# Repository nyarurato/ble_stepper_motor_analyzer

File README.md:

# BLE Stepper Motor Monitor

The BLE Stepper Monitor Analyzer is a variant of the Simple Stepper Motor Analyzer which replaces the touch screen LCD with a Bluetooth BLE radio link and a python app that provides the display or a desktop computer. This result in a smaller and less expensive board and a large display that leverages on the desktop computer capabilities.

## Highlights
* Open-source hardware, firmware, and software designs, with permissive license that allows commercial use and does not require attribution.
* A small and relatively inexpensive PCB that can be embedded in a 3D printer or CNC machine.
* Each PCB has a unique address and can be monitored individually.
* The PCB's can be ordered  from JLCPCB with all the parts preassembled, except for the the nrf52 BLE module that need to be soldered separately.
* The stepper motor is galvanically isolated from the analyzer's electronics which  minimizes potential interference or ground loops.
* The analyzer can be powered from any 4.5 to 30VDC source and consumes very little power, about 50mw. Even a single 9V battery can power it for many hours. Power is required only when monitoring the stepper and the stepper can be operates safely even if the PCB is not powered.

## Caveats
* At this time, updating the PCB firmware requires a programmer. Normally it can be an inexpensive Segger JLink EDU Mini, which as of Aug 2022 are unavailable due to the global supply chain shortage. A more expensive alternative is the Nordic nRF52832 DK which can act also as a Segger programmer.
* The two current sensor ICs that are available from JLCPCB have higher noise than the Alegro GMR sensors. However, the analyzer functions properly with the noisier sensors as well.
* As of Aug 2022, the python application requires some TLC, for example to recover gracefully if a wireless connection lost. However, it is fully functional and was tested on Windows and Mac OSX.
* The PCB can be built with two versions of the BLE module, one with an internal antenna and one with a U.FL connector for an external antenna. Internal antennas are 
more compact but may be insufficient with shielded 3D printers.

## Installing the PCB

* IMPORTANT: Always turn power off before connecting or disconnecting the PCB or the stepper motor.
* Connect a voltage of 4.5VDC t0 30VDC to the connector J3. Pay attention to polarity though the PCB is protected against reversed polarity. Verify that one red LED is solid while the other blinks slowly.;
* With the PCB energized and the **stepper not connected yet to the board** long press on the PCB button until the yellow LED will blink. Make sure the LED blinked exactly 3 times. This will calibrate the zero current of the sensors.
* With power off, connect the 4 wires of your stepper motor through the board such that one connector with four wires is connected to your controller and the other is connected to the stepper. The PCB is arranged such that the 4 connector pins from left to right are connected pass-through to their respective pins on the other connector. Also, the two connector are interchangeable such that each can act as an input or an output.
* Turn power on and verify that your machine functions properly and that the direction of the stepper is correct. That is, the wiring should not reverse the direction of the stepper.

## Installing and running the Python application.

1. Download the python directory this github repository.
1. Install python3 on your computer. Follow the Python installation instructions for your operating system. The analyzer requires Python 3.7 or latter but prefer the latest available python. 
1. Identify the *python* and *pip* command on your computer. On some computers they can be *python* and *pip* respectively and on others something like *python3.10& and *pip3.10* respectively. From now on we will refer to them as *python* and *pip* but replace with the actual command names as needed.
1. Verify the version of your python by running the command: **python --version**. Verify that the printed version number is at least 3.7.
1. With the PCB powered, Run the command  *python3 scanner_main.py*, after a few seconds, it will print a list of BLE devices it found. One of them should have the name that looks like STP-XXXXXXXXXXXX. Note the device
address that is printed before that name. We will use it later to access
the device.
1. Run the command **python analyzer_main.py -d <device-address>** where <device-address> is the device address you identified in the previous step. If you get errors about missing python modules such as **bleak**, install them using the pip command and try again. You can also use the
**requirements.txt** file to install all missing modules at once.
1. If everything went well, the analyzer_main.py application will connect to the device and shows its data in real time.

## Understanding the data
The screenshot below shows the 8 data items that are monitors. The data can be reset using the **Reset** button and can be paused/played using the **Pause/Continue** button. 

1. Step counter over time. If the direction of the counting is opposite to what you would like, click on the **Toggle Dir** button. This will not effect the stepper motor but will count in the opposite direction.
2. Speed in steps/sec over time. This value is the derivative of the step counter above.
3. Stepper current in Amps over time. This value is computed as *sqrt(A^2 + B^2)* where A and B are the momentary currents in Amps in coils A, B respectively, and it represents the peak currents in each of the coils.
4. Coil peak current vs speed. This histogram shows the stepper current in different speeds. Ideally all speeds should have about the same current but too high inductance or too lower supply voltage may result in current and torque degradation in higher speeds.
5. Distance vs speed. This histogram shows in what speeds the stepper made the most distance (steps or revolutions)
6. Time vs speed. This histogram shows in what speeds the stepper was most of the time.
7. Phase pattern. This graph shows the 'cleanness' of the signal in the stepper coil. Every second of two the analyzer captures the signals in graph 8 and shows their pattern also in graph 7. Ideally graph 7 would be a circle center around the 0,0 point and its radius is the peak current set for the stepper.
8. Oscilloscope graph. This graph shows current patterns captures periodically from the two coils and ideally they should look like clean sin/cosine graphs with magnitude equal to the stepper peak current. Every cycle of the sin/cosine graph represent 4 full stepper steps. If the stepper speed is too fast or two slow to show the signals, use the Time Scale button to speed up or slow down the signal capture.

## Building your own BLE Stepper Motor Analyzer

* The three production files for JLCPCB SMD service are available under the kicad directory. This will allow you to get fully populated boards except for the BLE module.
* Solder a Raytac nrf52832 BLE module. You can use MDBT42Q-512KV2 (internal antenna) or MDBT42Q-U512KV2 (U.FL connector for an external antenna).
* Flash the board with the firmware using a compatible SWD programmer. We are using Segger's JLink with a Segger Edu Mini programmer or if this is not available, a Nordic NRF52-DK which can act also as a JLink programmer. Use a standard 2x5 pins 0.05" pitch SWD cable.
* Zero calibrate the sensors as explained above. 

## Modifying the firmware

* The source code of the firmware is available in this github repository under the platformio folder. Open that folder with the platformio IDE (a plugin for VSCode) and your project is ready.
* The PCB has a serial output for debugging. You can connect there a 115200 baud 3.3v serial/USB and view the output.
* To program the PCB use a Segger compatible debugger such as Segger Edu Mini, or Nordic nrf52 DK board. This will also allow you to debug the program, set breakpoints, single step and so on.

## FAQ

Q: Can I use this open source design in commercial products?

A: Yes, and you are welcome to do so, and attribution is not needed.

-----

Q: Can I operate the printer with the PCB connected but not powered or not monitored?

A: Yes. The electronics and the stepper are isolated from each other.

----

Q: How much does it cost to build the PCB?

A: Depending on quantities. For a batch of 30, JLCPCB changes about $7 per assembled board and then you need to add the Raytac BLE module which costs about $9. This brings the unit cost to less than $20, as of Aug 2022.

----

Q: If you would redesign it from scratch, what would you do differntly?

A: The main change would be to use ESP32 instead of the Raytac/Nordic module and this is for several reasons:

* It's less expensive.
* It has better support for firmware upgrade by the user.
* It's available from JLCPCB's SMD assembly service.

The Nordic nrf52 was selected for it's low power, with the intention to power the PCB by harvesting stepper motor power, but that requirement was dropped at a latter stages of the project.

-----

Q: How does this differs from the Simple Stepper Motor analyzer?

A: Some of the differences are:

* The lack of builtin display makes this analyzer more compact and less expensive.
* The Simple Stepper Motor analyzer is self contained with display while this one is intended to be buried in a 3D printer, using a computer for the display.
* The Simple Stepper Motor Analyzer uses a Raspberry Pi Pico processor while this one uses Nordic nRF52832.
* The Simple Stepper Motor Analyzer samples the signal at 100Khz while this one samples at 40Khz due to the limitations of the nRF52832. This however doesn't seem to matter.
* The Simple Stepper Motor Analyzer displays each graph on screen of its own while this one displays all the graphs at once.
* Having the display on a computer makes it easier to graph screenshots, for example, to post in diagnostics discussions in 3D printer forums.

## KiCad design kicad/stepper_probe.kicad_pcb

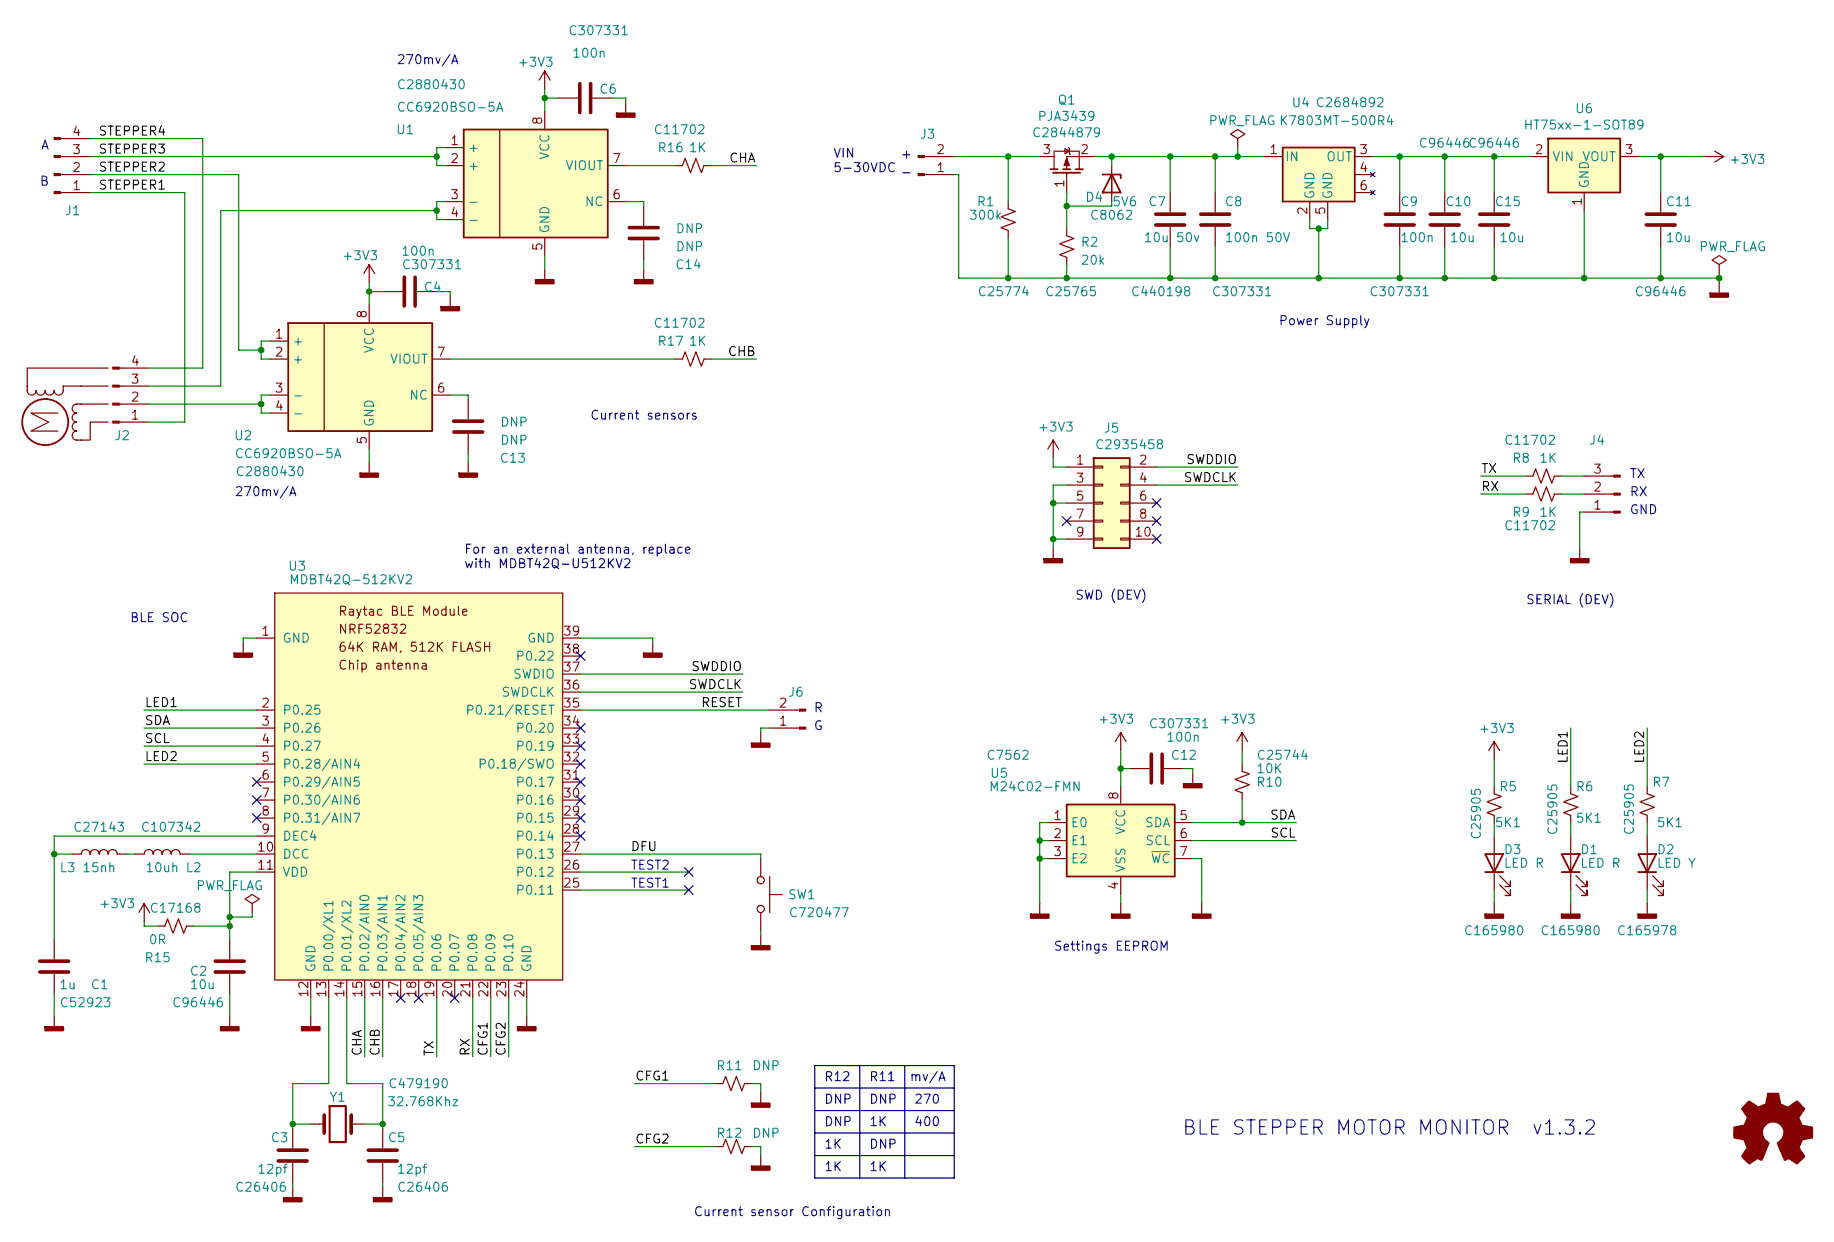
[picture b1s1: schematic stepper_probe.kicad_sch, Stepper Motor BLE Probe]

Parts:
C1: 1u; C_0402_1005Metric_Pad0.74x0.62mm_HandSolder; LCSC C52923
C2, C10, C11, C15: 10u; C_0603_1608Metric_Pad1.08x0.95mm_HandSolder; LCSC C96446
C3, C5: 12pf; C_0402_1005Metric_Pad0.74x0.62mm_HandSolder; LCSC C26406
C4, C6, C9, C12: 100n; C_0402_1005Metric_Pad0.74x0.62mm_HandSolder; LCSC C307331
C7: 10u 50v; C_0805_2012Metric_Pad1.18x1.45mm_HandSolder; LCSC C440198
C8: 100n 50V; C_0402_1005Metric_Pad0.74x0.62mm_HandSolder; LCSC C307331
C13, C14: DNP; C_0402_1005Metric_Pad0.74x0.62mm_HandSolder; LCSC DNP
D1, D3: LED R; LED_0402_1005Metric_Pad0.77x0.64mm_HandSolder; LCSC C165980
D2: LED Y; LED_0402_1005Metric_Pad0.77x0.64mm_HandSolder; LCSC C165978
D4: 5V6; D_MiniMELF_zenner; LCSC C8062
J1, J2: Conn_01x04_Male; connector_4pins_horizontal; LCSC C31753
J3: BAT; PinHeader_1x02_P2.54mm_Horizontal_JLCPCB; LCSC C2935927
J4: Conn_01x03_Male; PinHeader_1x03_P2.54mm_Vertical; LCSC C49257
J5: SWD; PinHeader_2x05_P1.27mm_Vertical_SMD; LCSC C2935458
J6: Reset header; PinHeader_1x02_P2.54mm_Vertical; LCSC DNP
L2: 10uh; coil_10uh; LCSC C107342
L3: 15nh; C_0402_1005Metric_Pad0.74x0.62mm_HandSolder; LCSC C27143
M1: Motor; Empty; LCSC DNP
Q1: PJA3439; SOT-23_JLCPCB; LCSC C2844879
R1: 300k; R_0402_1005Metric_Pad0.72x0.64mm_HandSolder; LCSC C25774
R2: 20k; R_0402_1005Metric_Pad0.72x0.64mm_HandSolder; LCSC C25765
R5, R6, R7: 5K1; R_0402_1005Metric_Pad0.72x0.64mm_HandSolder; LCSC C25905
R8, R9, R16, R17: 1K; R_0402_1005Metric_Pad0.72x0.64mm_HandSolder; LCSC C11702
R10: 10K; R_0402_1005Metric_Pad0.72x0.64mm_HandSolder; LCSC C25744
R11, R12: DNP; R_0402_1005Metric_Pad0.72x0.64mm_HandSolder; LCSC DNP
R15: 0R; R_0402_1005Metric_Pad0.72x0.64mm_HandSolder; LCSC C17168
SW1: SW_Push; SW_Push_SPST_NO_Alps_SKRK; LCSC C720477
U1, U2: CC6920BSO-5A; SOIC-8_LCPCB_ROT; LCSC C2880430
U3: MDBT42Q-512KV2; RAYTAC_MDBT42Q
U4: K7803MT-500R4; Converter_DCDC; LCSC C2684892
U5: M24C02-FMN; SOIC-8_LCPCB_ROT; LCSC C7562
U6: HT75xx-1-SOT89; SOT-89-3; LCSC C14289
Y1: 32.768Khz; Crystal_SMD_3215-2Pin_3.2x1.5mm; LCSC C479190

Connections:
+3V3: C4.2, C6.2, C11.1, C12.2, J5.1, R5.2, R10.2, R15.2, U1.8 (VCC), U2.8 (VCC), U5.8 (VCC), U6.3 (VOUT)
/CFG1: R11.1, U3.22 (P0.09)
/CFG2: R12.1, U3.23 (P0.10)
/CHA: R16.1, U3.15 (P0.02/AIN0)
/CHB: R17.1, U3.16 (P0.03/AIN1)
/DFU: SW1.1, U3.27 (P0.13)
/LED1: R6.2, U3.2 (P0.25)
/LED2: R7.2, U3.5 (P0.28/AIN4)
/RESET: J6.2, U3.35 (P0.21/RESET)
/RX: R9.2, U3.21 (P0.08)
/SCL: U3.4 (P0.27), U5.6 (SCL)
/SDA: R10.1, U3.3 (P0.26), U5.5 (SDA)
/STEPPER1: J1.1, J2.1
/STEPPER2: J1.2, U2.1 (+), U2.2 (+)
/STEPPER3: J1.3, U1.1 (+), U1.2 (+)
/STEPPER4: J1.4, J2.4
/SWDCLK: J5.4, U3.36 (SWDCLK)
/SWDDIO: J5.2, U3.37 (SWDIO)
/TX: R8.2, U3.19 (P0.06)
GND: C1.2, C2.2, C3.2, C4.1, C5.2, C6.1, C7.2, C8.2, C9.2, C10.2, C11.2, C12.1, C13.1, C14.1, C15.2, D1.1 (K), D2.1 (K), D3.1 (K), J3.1, J4.1, J5.3, J5.5, J5.9, J6.1, R1.1, R2.1, R11.2, R12.2, SW1.2, U1.5 (GND), U2.5 (GND), U3.1 (GND), U3.12 (GND), U3.24 (GND), U3.39 (GND), U4.2 (GND), U4.5 (GND), U5.1 (E0), U5.2 (E1), U5.3 (E2), U5.4 (VSS), U5.7 (~WC), U6.1 (GND)
unnamed: C1.1, L3.2, U3.9 (DEC4)
unnamed: C2.1, R15.1, U3.11 (VDD)
unnamed: C3.1, U3.13 (P0.00/XL1), Y1.1
unnamed: C5.1, U3.14 (P0.01/XL2), Y1.2
unnamed: C7.1, C8.1, D4.1 (K), Q1.2 (S), U4.1 (IN)
unnamed: C9.1, C10.1, C15.1, U4.3 (OUT), U6.2 (VIN)
unnamed: C13.2, U2.6 (NC)
unnamed: C14.2, U1.6 (NC)
unnamed: D1.2 (A), R6.1
unnamed: D2.2 (A), R7.1
unnamed: D3.2 (A), R5.1
unnamed: D4.2 (A), Q1.1 (G), R2.2
unnamed: J2.2, U2.3 (-), U2.4 (-)
unnamed: J2.3, U1.3 (-), U1.4 (-)
unnamed: J3.2, Q1.3 (D), R1.2
unnamed: J4.2, R9.1
unnamed: J4.3, R8.1
unnamed: L2.1, U3.10 (DCC)
unnamed: L2.2, L3.1
unnamed: R16.2, U1.7 (VIOUT)
unnamed: R17.2, U2.7 (VIOUT)

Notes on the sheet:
VIN 5-30VDC
270mv/A
mv/A
Current sensor Configuration
DNP
270
TEST2
BLE SOC
Power Supply
Settings EEPROM
SWD (DEV)
For an external antenna, replace with MDBT42Q-U512KV2
R12
TEST1
400
GND
R11
Current sensors
BLE STEPPER MOTOR MONITOR v1.3.2
SERIAL (DEV)

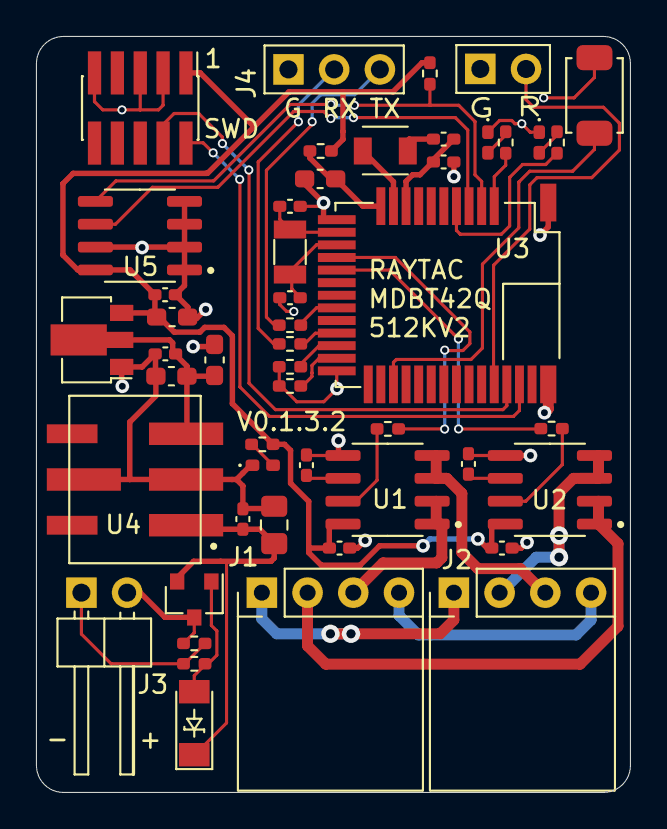
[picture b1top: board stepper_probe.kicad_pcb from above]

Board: 2 copper layers, 33.0 x 42.0 mm, 50 parts (0 on the bottom side), 41 nets.

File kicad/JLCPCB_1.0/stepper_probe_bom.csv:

Comment,Designator,Footprint, LCSC Part Number
1u,C1 ,SMD 0402,C52923
10u 25V,C10 C11 ,SMD 0603,C96446
10u,C2 ,SMD 0603,C96446
12pf,C3 C5 ,SMD 0402,C26406
0.1u,C4 C6 ,SMD 0402,C307331
10u 50v,C7 ,SMD 0805,C440198
0.1u 50V,C8 C9 ,SMD 0402,C307331
LED Green/Yellow,D1,SMD 0402,C165979
LED Red,D2,SMD 0402,C165980
LED Yellow,D3 ,SMD 0402,C165978
MB1S,D4 D5 ,SOIC 4,C232821 
1N5819WS,D6 ,SOD-323,C191023
Conn_01x04_Male,J1 J2 ,Molex 2.54 x 4,C31753
SWD,J5 ,Header 2x5 1.27mm SWD,C239059
10uh,L2 ,Coil 10uh,C107342
15nh,L3 ,SMD 0402,C27143
AO3401A,Q1 ,SOT-23,C15127
10R,R1 R2 R3 R4 ,SMD 0402,C25077
5K1,R5 R6 R7 ,SMD 0402,C25905
1K,R8 R9 ,SMD 0402,C11702
32.768Khz,Y1 ,Crystal,C479190

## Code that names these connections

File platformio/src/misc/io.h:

#pragma once

#include <hal/nrf_gpio.h>
#include <stdint.h>
#include <zephyr.h>
// #include <misc/button.h>

namespace io {

// --- Output pins

class OutputPin {
 public:
  // Note: Constructor is not called. Seems to be related to the
  // fact we use this as a global var.
  OutputPin() {}

  void init(uint32_t pin_num, uint32_t initial_state) {
    // printk("** OutputPin.init(%u), prior=%u\n", pin_num, pin_num_);
    pin_num_ = pin_num;
    nrf_gpio_cfg_output(pin_num_);
    write(initial_state);
  }
  inline void set() { nrf_gpio_pin_set(pin_num_); }
  inline void clear() { nrf_gpio_pin_clear(pin_num_); }
  inline void toggle() { nrf_gpio_pin_toggle(pin_num_); }
  inline void write(uint32_t val) { nrf_gpio_pin_write(pin_num_, val); }
  inline uint32_t pin_num() { return pin_num_; }

 private:
  // Initialized by init().
  uint32_t pin_num_ = 0;
};

// Active low.
extern OutputPin LED1;
extern OutputPin LED2;

// Output pulses for diagnostics.
extern OutputPin TIMER_OUT_PIN;
extern OutputPin ISR_OUT_PIN;

// Enables power on 0 value.
// extern OutputPin<9> SENSOR_POWER_PIN;

// --- Output pins

class InputPin {
 public:
  InputPin() {}
  void init(uint32_t pin_num, nrf_gpio_pin_pull_t pull) {
    pin_num_ = pin_num;
    nrf_gpio_cfg_input(pin_num_, pull);
  }
  inline bool read() { return nrf_gpio_pin_read(pin_num_); }
  inline bool is_high() { return read(); }
  inline bool is_low() { return !read(); }
  inline uint32_t pin_num() { return pin_num_; }

 private:
  // Initialized by init()
  uint32_t pin_num_ = 0;
};

// Active low. This pin is also the default DFU switch pin
// of MCUboot.
extern InputPin SWITCH1;

// Used to select hardware configuration based on population
// of resistors R11, R12. An installed resistor results in
// '0' at the respective input.
extern InputPin HARDWARE_CFG1;
extern InputPin HARDWARE_CFG2;


void setup();

// Read hardware configuration.
// Returns:
// 3 - R11, R12, not installed.
// 2 - Only R11 installed.
// 1 - Only R12 installed.
// 0 - Both R11, R12 installed.
extern uint8_t read_hardware_config();

}  // namespace io

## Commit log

2022-07-18 Initial public version. No official release yet.
2022-07-18 More PCB cleanup.
2022-07-19 Generated 3D view.
2022-07-19 Generated gerber files.
2022-07-19 Generated production files. No tested yet.
2022-07-19 Production files with JLCPCB order.
2022-08-02 Updated pin and address to the new JLCPB board.
2022-08-03 Added calibration battery pads.
2022-08-03 Added config eeprom r/w
2022-08-06 Added support for zero calibration and direction change via the button.
2022-08-06 Freed LED2 for future user feedback.
2022-08-06 Added configuration resistors.
2022-08-06 Moved SOIC footprint to local library. Before rotating for JLCPCB.
2022-08-06 Rotated footprints for JLCPCB orientation.
2022-08-07 Added setting of capture divider.
2022-08-07 Added command to control capture divider.
2022-08-08 Assorted tweaks.
2022-08-08 Change capture divider from uint16 to unt8
2022-08-08 Updated todos.
2022-08-08 Added the stepper connectors to JLCPCB files.
2022-08-08 Added stepper connectors to JLCPCB list.
2022-08-09 Minor cleanup.
2022-08-10 Work in progress.
2022-08-13 Minor clean ups.
2022-08-13 Cleaned up power in header.
2022-08-13 Generated gervers.
2022-08-13 Minor change of 'DNI' to 'DNP' for consistency.
2022-08-14 Added zener protection
2022-08-14 Generated JLCPCB gerber files.
2022-08-14 Updated TODO, added noise analysis.
2022-08-14 Fixed a few TODOs.
2022-08-15 Added UI feedback via LED2.
2022-08-15 Added direction to fractional step computation.
2022-08-15 Minor PCB tweaks, moved LEDs, added pin 1 marks, added zenner silk screen. No electrical or bom change.
2022-08-16 Added BLE command for direction toggle and zero calibration.
2022-08-20 Added screen capture video.
2022-08-20 Added sensors selection logic. Tweaked the python client.
2022-08-21 Tweaks
2022-08-23 Added phase graph + assorted tweaks.
2022-08-24 Inverted the hardware config code.
2022-08-25 Added reporting of is_energized.
2022-08-26 Cleaned up the event loop.
2022-08-26 Added requirements files. Remove initial delayed. Reduced timer interval from 25ms to 20ms.
2022-08-26 Added python flag for max amps. Updated TODO.
2022-08-28 Assorted tweaks and fixes.
2022-08-28 Added a script to run analyzer on mac.
2022-08-28 Now using average for zero calibration. Also updated README and Kicad.
2022-08-28 Fixed nrf52 footprint.
2022-08-29 Added unit scaling to the python app.
2022-08-30 Added an input test. Not used.
2022-08-31 Added 3 pins header to the JLCPCB BOM.
2022-08-31 Flushing open files.
2022-09-01 Commented out code for testing. No semantic change.
2022-09-06 Upgraded to kicad 6
2022-09-07 Cleaned up kicad 6 files.
2022-09-18 Minor kicad tweaks.
2022-09-18 Added print messages for debugging.
2022-09-24 Added additional debug markers to probe.py
2022-09-24 Refined debug messages.
2022-10-02 Updated to latest python and python packages. 1. scanner_main should work. Removed the timeout argument. 2. Adapted analyzer_main to latest pyqtgraph widgets.
    Tested with python 3.10.7 on windows 10, with pythong packages listed
    in requirements.txt.
2022-10-02 Adapted the scanner to the recomanded API.
2022-10-02 Added a test case for Bleak's connection.
2022-10-23 Changed the initialization order. Now first connecting to the device and then initializing pyqtgraph UI. This will make the initialization sequence closer to the one in the bleak test program which w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
2022-10-23 Now printing os and python info on start.
